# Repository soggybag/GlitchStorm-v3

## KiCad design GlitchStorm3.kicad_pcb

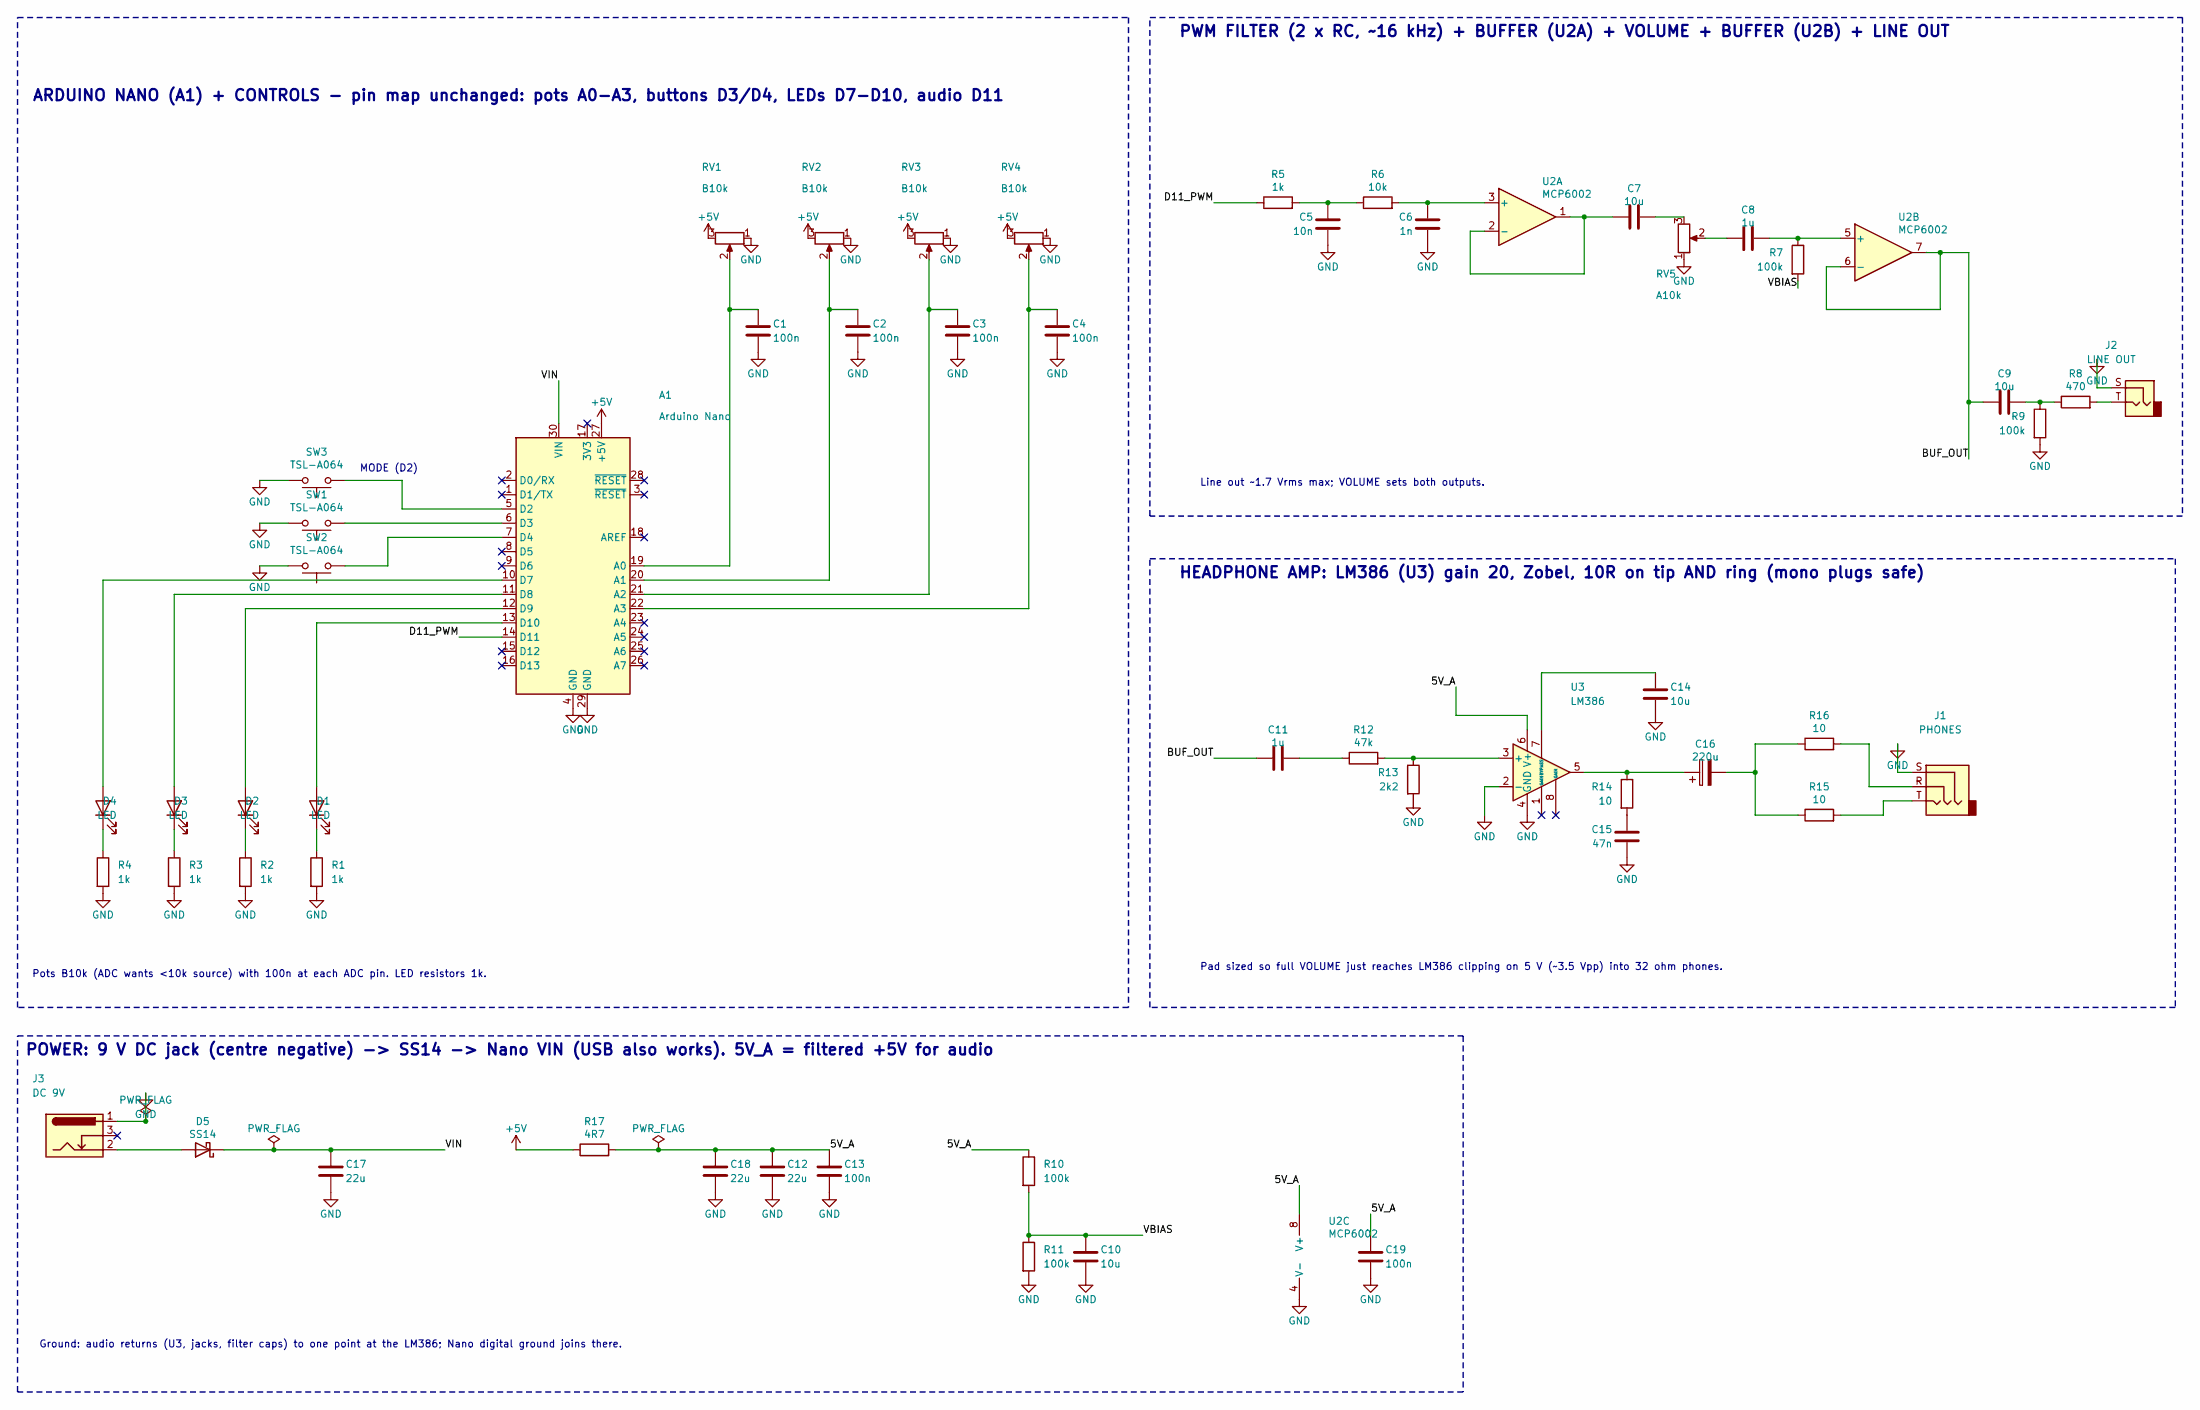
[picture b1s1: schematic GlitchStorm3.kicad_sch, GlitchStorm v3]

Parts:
A1: Arduino Nano; Arduino_Nano
C1, C2, C3, C4, C13, C19: 100n; C_0805_2012Metric_Pad1.18x1.45mm_HandSolder; LCSC C49678
C5: 10n; C_0805_2012Metric_Pad1.18x1.45mm_HandSolder; LCSC C1710
C6: 1n; C_0805_2012Metric_Pad1.18x1.45mm_HandSolder; LCSC C46653
C7, C9, C10, C14: 10u; C_0805_2012Metric_Pad1.18x1.45mm_HandSolder; LCSC C15850
C8, C11: 1u; C_0805_2012Metric_Pad1.18x1.45mm_HandSolder; LCSC C28323
C12, C17, C18: 22u; C_1206_3216Metric_Pad1.33x1.80mm_HandSolder; LCSC C12891
C15: 47n; C_0805_2012Metric_Pad1.18x1.45mm_HandSolder; LCSC C53134
C16: 220u; CP_Radial_D6.3mm_P2.50mm
D1, D2, D3, D4: LED; LED_D3.0mm
D5: SS14; D_SMA_Handsoldering; LCSC C2480
J1: PHONES; Jack_3.5mm_PJ-320A_Horizontal
J2: LINE OUT; Jack_3.5mm_PJ-320A_Horizontal
J3: DC 9V; BarrelJack_Horizontal
R1, R2, R3, R4, R5: 1k; R_0805_2012Metric_Pad1.20x1.40mm_HandSolder; LCSC C17513
R6: 10k; R_0805_2012Metric_Pad1.20x1.40mm_HandSolder; LCSC C17414
R7, R9, R10, R11: 100k; R_0805_2012Metric_Pad1.20x1.40mm_HandSolder; LCSC C17407
R8: 470; R_0805_2012Metric_Pad1.20x1.40mm_HandSolder; LCSC C17710
R12: 47k; R_0805_2012Metric_Pad1.20x1.40mm_HandSolder; LCSC C17713
R13: 2k2; R_0805_2012Metric_Pad1.20x1.40mm_HandSolder; LCSC C17520
R14, R15, R16: 10; R_0805_2012Metric_Pad1.20x1.40mm_HandSolder; LCSC C17415
R17: 4R7; R_0805_2012Metric_Pad1.20x1.40mm_HandSolder; LCSC C17675
RV1, RV2, RV3, RV4: B10k; Potentiometer_Alpha_RD901F-40-00D_Single_Vertical
RV5: A10k; Potentiometer_Alpha_RD901F-40-00D_Single_Vertical
SW1, SW2, SW3: TSL-A064; SW_Push_Round_D12mm_P5.00mm_DAIER_TSL-A064
U2: MCP6002; SOIC-8_3.9x4.9mm_P1.27mm; LCSC C7377
U3: LM386; SOIC-8_3.9x4.9mm_P1.27mm; LCSC C23573

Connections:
+5V: A1.27 (+5V), R17.1, RV1.3, RV2.3, RV3.3, RV4.3
/BUF_OUT: C9.1, C11.1, U2.6 (-), U2.7
/D11_PWM: A1.14 (D11), R5.1
/VBIAS: C10.1, R7.2, R10.2, R11.1
unnamed: A1.19 (A0), C1.1, RV1.2
unnamed: A1.20 (A1), C2.1, RV2.2
unnamed: A1.21 (A2), C3.1, RV3.2
unnamed: A1.22 (A3), C4.1, RV4.2
unnamed: A1.5 (D2), SW3.1
unnamed: A1.6 (D3), SW1.1
unnamed: A1.7 (D4), SW2.1
unnamed: A1.10 (D7), D4.2 (A)
unnamed: A1.11 (D8), D3.2 (A)
unnamed: A1.12 (D9), D2.2 (A)
unnamed: A1.13 (D10), D1.2 (A)
unnamed: C5.1, R5.2, R6.1
unnamed: C7.2, RV5.3
unnamed: C8.1, RV5.2
unnamed: C9.2, R8.1, R9.1
unnamed: C11.2, R12.1
unnamed: C15.1, R14.2
unnamed: C16.1, R14.1, U3.5
unnamed: C16.2, R15.1, R16.1
unnamed: D1.1 (K), R1.1
unnamed: D2.1 (K), R2.1
unnamed: D3.1 (K), R3.1
unnamed: D4.1 (K), R4.1
unnamed: D5.2 (A), J3.2
unnamed: J1.R, R16.2
unnamed: J1.T, R15.2
unnamed: J2.T, R8.2
unnamed: C6.1, R6.2, U2.3 (+)
unnamed: C7.1, U2.1, U2.2 (-)
unnamed: C8.2, R7.1, U2.5 (+)
unnamed: R12.2, R13.1, U3.3 (+)
unnamed: C14.1, U3.7 (BYPASS)

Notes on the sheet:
Pots B10k (ADC wants <10k source) with 100n at each ADC pin. LED resistors 1k.
Line out ~1.7 Vrms max; VOLUME sets both outputs.
ARDUINO NANO (A1) + CONTROLS - pin map unchanged: pots A0-A3, buttons D3/D4, LEDs D7-D10, audio D11
MODE (D2)
Ground: audio returns (U3, jacks, filter caps) to one point at the LM386; Nano digital ground joins there.
HEADPHONE AMP: LM386 (U3) gain 20, Zobel, 10R on tip AND ring (mono plugs safe)
PWM FILTER (2 x RC, ~16 kHz) + BUFFER (U2A) + VOLUME + BUFFER (U2B) + LINE OUT
POWER: 9 V DC jack (centre negative) -> SS14 -> Nano VIN (USB also works). 5V_A = filtered +5V for audio
Pad sized so full VOLUME just reaches LM386 clipping on 5 V (~3.5 Vpp) into 32 ohm phones.

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
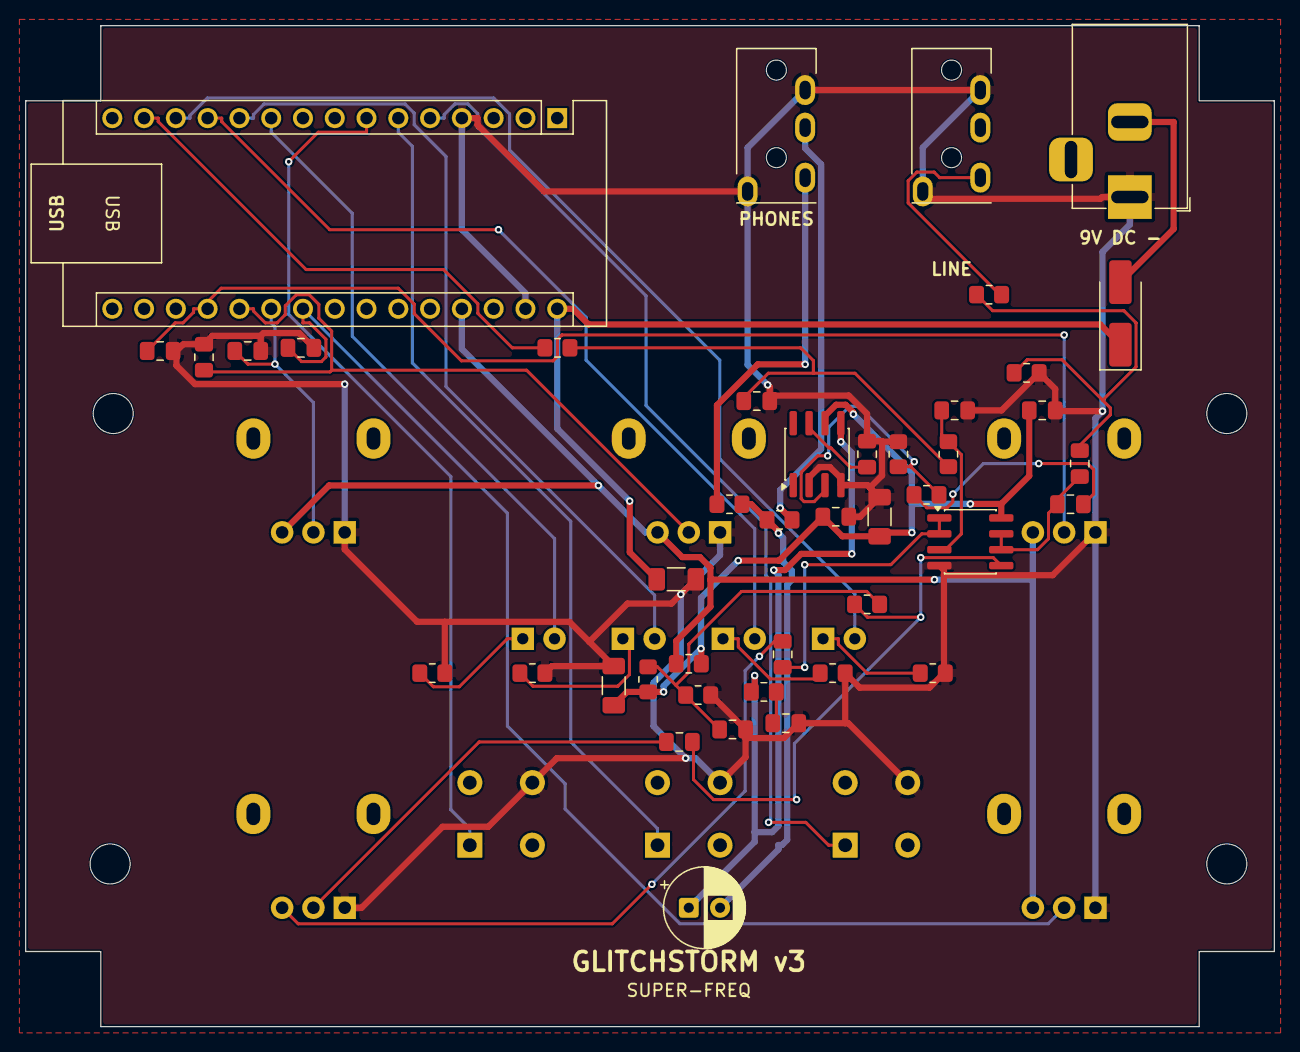
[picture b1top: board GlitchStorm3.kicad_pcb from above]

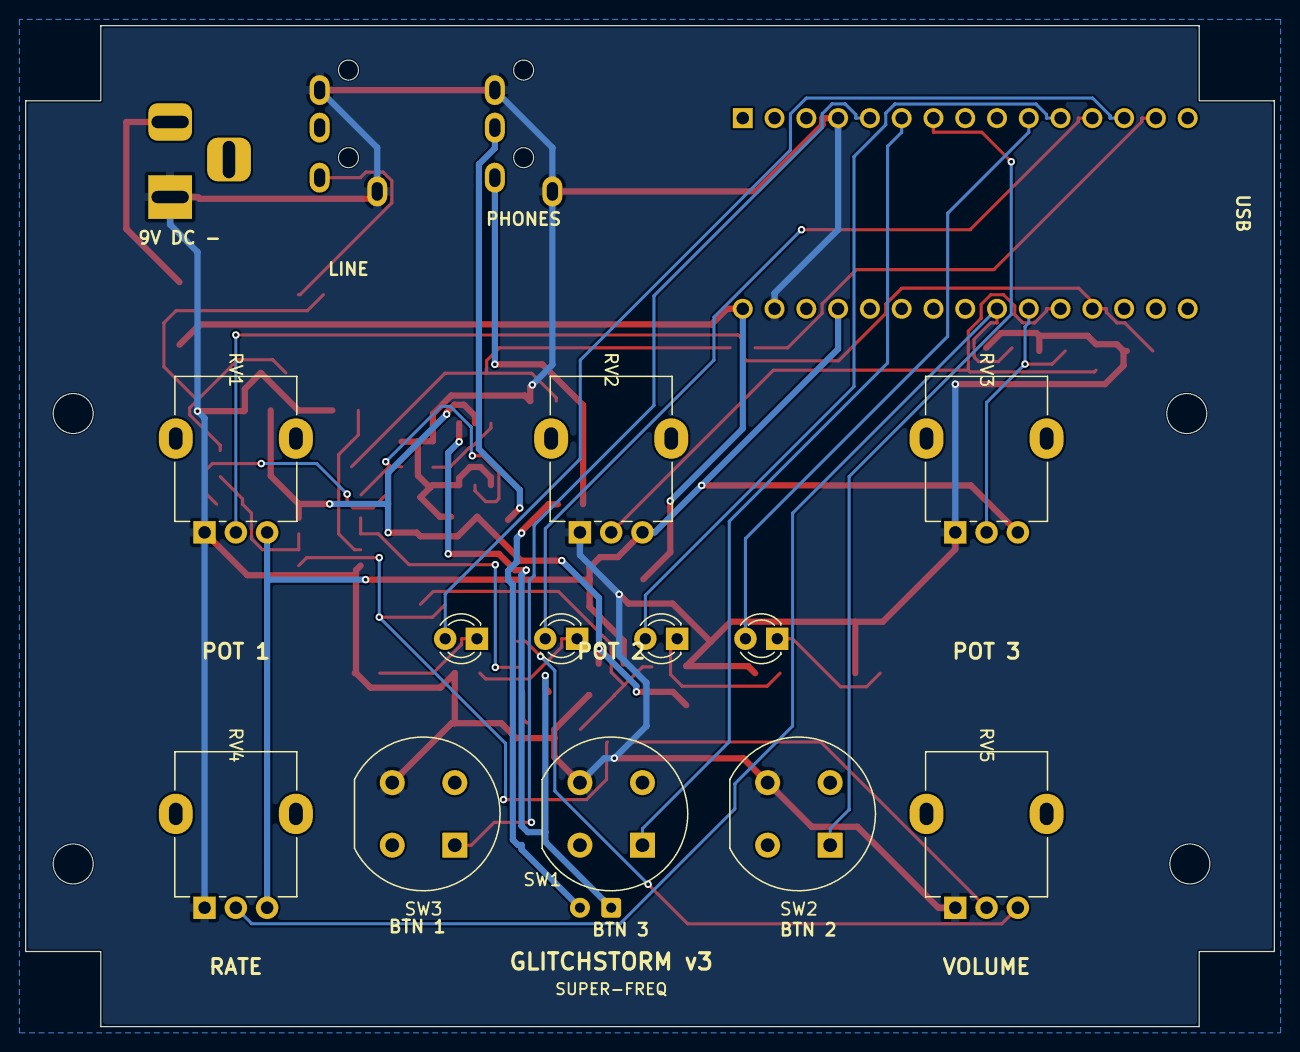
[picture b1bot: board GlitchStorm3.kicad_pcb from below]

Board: 2 copper layers, 99.8 x 80.0 mm, 60 parts (12 on the bottom side), 39 nets.

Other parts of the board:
ENC1: Hammond_1590BB
H1, H2, H3, H4: MountingHole_3.2mm_M3
